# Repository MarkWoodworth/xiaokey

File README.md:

# xiaoKey

Even yet another electronic iambic keyer. 

It is a minimalist device based on:

* an inexpensive Seeed [Xiao](https://www.seeedstudio.com/XIAO-RP2040-v1-0-p-5026.html) RP2040 controller board
* [CircuitPython](https://circuitpython.org/) programs and libraries

The `code` directory has the files to be installed on the *Seeed Xiao* device.

The `pcb`directory has the Eagle schematics for a possible carrier board with connectors.

## Features

* Operates as an [iambic type B](http://wb9kzy.com/modeab.pdf) Morse code keyer with a 3.5mm stereo jack to connect to a dual-paddle telegraph key
* Has a configurable side tone transmitted through an on-board piezo buzzer
* Has an open-drain output to a 2.5mm mono jack, which should be able to key most radios (probably not tube sets)
* When connected to a PC over USB appears as two COM ports:
  * One is the *CircuitPython* REPL and console
  * A second port that shows the characters being transmitted, and also transmits Morse code for characters typed into the COM port
* Has three buttons to trigger canned messages
* Speed, sidetone, keyboard operation, and canned messages are configured by editing the `code.py` file on the *CIRCUITPY:* device
* Can act as a USB keyboard, where keyed characters are also sent to the computer as keystrokes.  

## Software Installation

1. Get the most recent UF2 file for *CircuitPython* on the *Xiao RP2040* [here](https://circuitpython.org/board/seeeduino_xiao_rp2040/).

2. Connect the *Xiao* to a computer using a USB C cable.

3. Follow the instructions for loading *CircuitPython* [here](https://wiki.seeedstudio.com/XIAO-RP2040-with-CircuitPython/).  Basically, you put the *Xiao* in boot loader mode by pressing and holding the _BOOT_ button and tapping the reset button.   Then copy the UF2 file to the *Xiao* which appears as `RP1-RP2`. The *Xiao* will now reboot itself.

4. Copy the required library files (in the repository `lib` directory) to the `lib` directory on the attached *Xiao*.  The files are:

   * `neopixel.mpy`
   * The directory `adafruit_hid`

   The most recent versions of these files can be found [here](https://circuitpython.org/libraries).

5. Copy `boot.py` and `code.py` to the Xiao, which now appears as drive `CIRCUITPY` on the computer.

6. Press the *RESET* button on the Xiao.

## Configuration

The device is configured by editing the source file `code.py` on the *Xiao* device.  The configuration parameters appear near the top.

```python
# user configuration
WPM = 15
SIDETONE = True
SIDEFREQ = 880
KEYBOARD = False

# user messages
MSG1 = "AC9YW"
MSG2 = "CQ CQ CQ DE AC9YW AC9YW AC9YW K"
MSG3 = "73"
```

* `SIDETONE` True will generate a tone on the buzzer when keying,  False will disable the local side tone.
* `SIDEFREQ` is the audio frequency of the side tone sound in Hz. 880 should sound like the musical note A an octave above concert A.  The frequency you choose is simply a matter of preference.
* `KEYBOARD` True will type decoded characters into the attached computers as though typed on a keyboard. *Be careful turning this on, as your Morse keying will appear in whatever window currently has focus, which can have unintended effects.*
* `MSGx` Are the contents of the canned messages triggered by the on-board tact buttons

The file `code.py` should appear as a text file on the `CIRCUITPY:` device.  There are special programs to aid in editing Python programs (such as [Mu](https://codewith.mu/) and [Thonny](https://thonny.org/)) but most simple text editors should work.  *Avoid word processing programs that save files in special formats*.   A discussion of editors for CircuitPython can be found [here](https://learn.adafruit.com/welcome-to-circuitpython/recommended-editors).

You may have to reset the Xiao after editing for the changes to take effect.

## Pinout

```
                 +---USB C--+  
  paddle dit in  D0        5V
  paddle dah in  D1       GND
      buzzer pwm D2       3v3
         key out D3       D10 in  button 1
     i2c sda     D4        D9 in  button 2 
     i2c scl     D5        D8 in  button 3
          tx     D6        D7     rx
                 +----------+
```

## Schematic

## Bill of Materials

| Part     | Description                         | Link                                                         |
| -------- | ----------------------------------- | ------------------------------------------------------------ |
| U1       | Seeed Studio Xiao Controller RP2040 | https://www.seeedstudio.com/XIAO-RP2040-v1-0-p-5026.html     |
| J1       | 3.5mm Stereo Jack                   | https://www.digikey.com/en/products/detail/cui-devices/SJ1-3523N/738689 |
| J2       | 2.5mm Mono jack                     | https://www.digikey.com/en/products/detail/cui-devices/MJ1-2503A/738679 |
| Buzz     | Passive Piezo Buzzer                | https://www.amazon.com/gp/product/B018I1WBNQ/                |
| Q1       | 2N7000 n-channel MOSFET 60V TO92-3  | https://www.digikey.com/en/products/detail/onsemi/2N7000-D74Z/3478161 |
| C1       | Capacitor ceramic 0.1uF 50V         | https://www.digikey.com/en/products/detail/kemet/C315C103K5R5TA7303/3726109 |
| S1 S2 S3 | Tact switch SPST NO 6mm x 6mm       | https://www.digikey.com/en/products/detail/cit-relay-and-switch/CT11025-0F160/12418891 |
| Headers  | Header female 7 position 0.1 pitch  | https://www.digikey.com/en/products/detail/sullins-connector-solutions/PPTC071LFBN-RC/810146 |

Most of the parts are generic:  I have given the links to where I got them.  Note that not all audio jacks are created equal:  the pin locations can vary.

## Assembly

The only tricky part is soldering the castellated Xiao to the board. [Here](https://learn.sparkfun.com/tutorials/how-to-solder-castellated-mounting-holes/all) is a tutorial with video on soldering castellated parts.  I think I put too much solder on the first time I tried, and filled the through holes on the Xiao.  Not a real problem, but probably not best practice.  Also, definitely solder the Xiao on first, especially before the headers!  

Not all parts are required.

* For **minimal functionality**, solder on:

  * U1 Seeed Xiao controller

  * J1 3.5mm jack to Iambic key

* To have **local side tone generation**, add:
  * 9mm piezo buzzer (note polarity)
* To **key a radio** with a sinking open drain output (up to 50V), add:
  * Q1 n-channel MOSFET transistor
  * C1 0.1 ceramic capacitor (to lessen key clicks?)
  * J2 2.5mm mono jack (open drain on tip, ground on ring)
* To **trigger stored messages**:
  * Add S1, S2, and S3 tact switches
* To allow easy access to the Xiao pins **for expansion and experimentation**:
  * Add 7 position female headers

## Future

Some Ideas:

* The I2C pins are available to expand to other parts, including a display or other inputs
* The Rx and Tx pins are available to expand to a (3.3V level) serial port

## References

The iambic keyer state machine owes a great debt to the [1keyer](https://hackaday.io/project/18841-1keyer/log/50103-state-machine-of-the-union) project by Mark VandeWettering, and the [PIK](https://owenduffy.net/module/pik/pik.htm) project by Owen Duffy.

Larry Kuck (WB7C) has very helpful resources at [Morse Code for the Radio Amateur](https://www.morsecodeclassnet.com/)

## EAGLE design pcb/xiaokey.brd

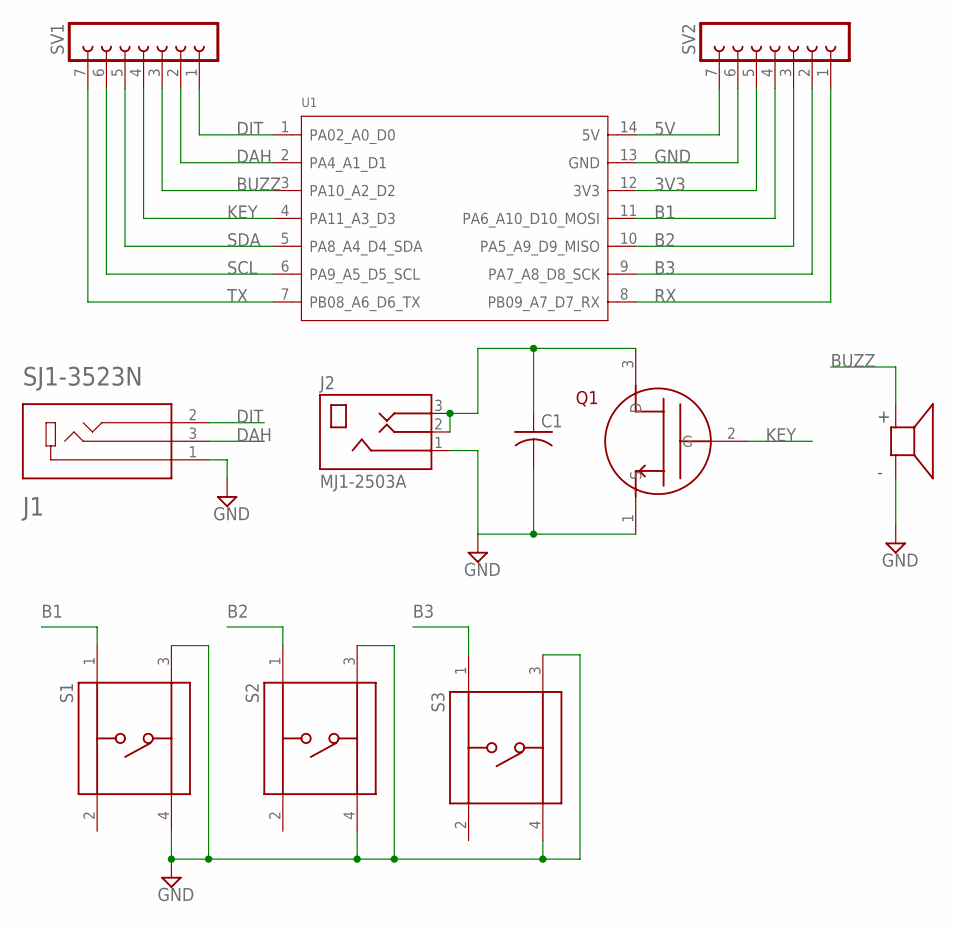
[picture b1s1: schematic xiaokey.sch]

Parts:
C1: C-US050-024X044; C050-024X044
J1: SJ1-3523N; CUI_SJ1-3523N
J2: MJ1-2503A; CUI_MJ1-2503A
LS1: AT-0927-TT-6-R; XDCR_AT-0927-TT-6-R
Q1: 2N7000; TO92-LINE
S1, S2, S3: TS02-66-60-BK-160-LCR-D; SW_TS02-66-60-BK-160-LCR-D
SV1, SV2: FE07-1; FE07
U1: MOUDLE-SEEEDUINO-XIAO; MOUDLE14P-2.54-21X17.8MM

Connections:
3V3: SV2.5, U1.12 (3V3)
5V: SV2.7, U1.14 (5V)
B1: S1.1, SV2.4, U1.11 (PA6_A10_D10_MOSI)
B2: S2.1, SV2.3, U1.10 (PA5_A9_D9_MISO)
B3: S3.1, SV2.2, U1.9 (PA7_A8_D8_SCK)
BUZZ: LS1.P, SV1.3, U1.3 (PA10_A2_D2)
DAH: J1.3, SV1.2, U1.2 (PA4_A1_D1)
DIT: J1.2, SV1.1, U1.1 (PA02_A0_D0)
GND: C1.2, J1.1, J2.1, LS1.N, Q1.1 (S), S1.3, S1.4, S2.3, S2.4, S3.3, S3.4, SV2.6, U1.13 (GND)
KEY: Q1.2 (G), SV1.4, U1.4 (PA11_A3_D3)
unnamed: C1.1, J2.2, J2.3, Q1.3 (D)
RX: SV2.1, U1.8 (PB09_A7_D7_RX)
SCL: SV1.6, U1.6 (PA9_A5_D5_SCL)
SDA: SV1.5, U1.5 (PA8_A4_D4_SDA)
TX: SV1.7, U1.7 (PB08_A6_D6_TX)

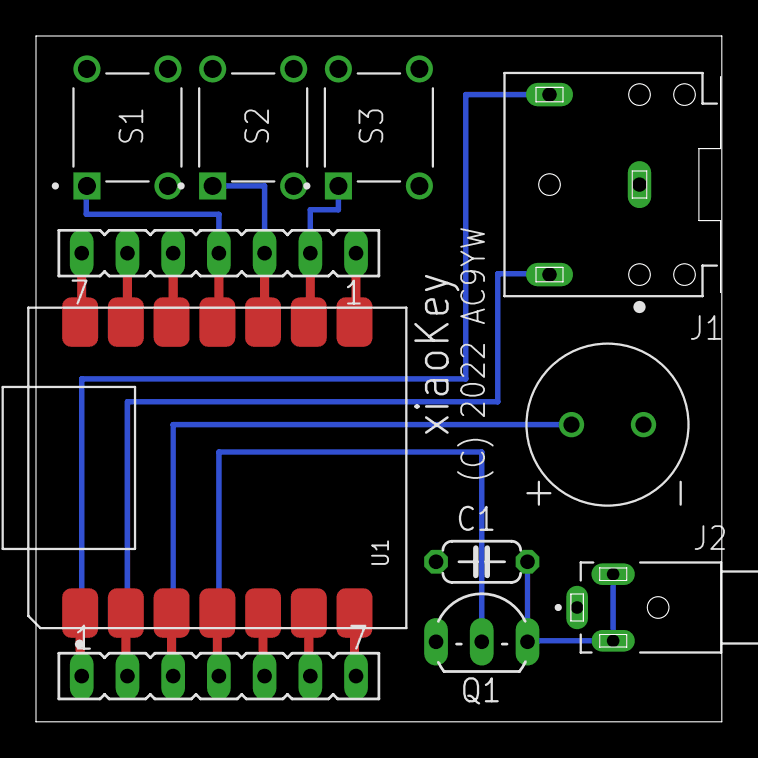
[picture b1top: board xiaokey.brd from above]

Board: 2 copper layers, 38.1 x 38.1 mm, 11 parts (0 on the bottom side), 15 nets.

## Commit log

2022-01-23 first
2022-01-25 swapped key and buzzer
2022-01-25 refactored Iambic class
2022-01-26 added prosigns
2022-01-26 shortend morse to map
2022-01-26 usde MAP rather than map
2022-01-27 added MIT license, changed led usage
2022-01-29 re-arranged directories, added pcb files, renamed keyer.py
2022-01-29 begin README file
2022-01-29 Edited README.md
2022-01-29 more edits
2022-01-29 Create LICENSE
2022-01-29 readme edits
2022-01-29 added schematic
2022-01-29 fixed image link
2022-01-29 added pcb image
2022-01-29 image resize
2022-02-02 added assembly photo
2022-02-02 swapped dit and dah inputs
2022-02-05 added BOM and notes to README
2022-02-06 mermaid test
2022-02-06 remove mermaid test

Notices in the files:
pcb/xiaokey.brd:
(C) 2022 AC9YW
